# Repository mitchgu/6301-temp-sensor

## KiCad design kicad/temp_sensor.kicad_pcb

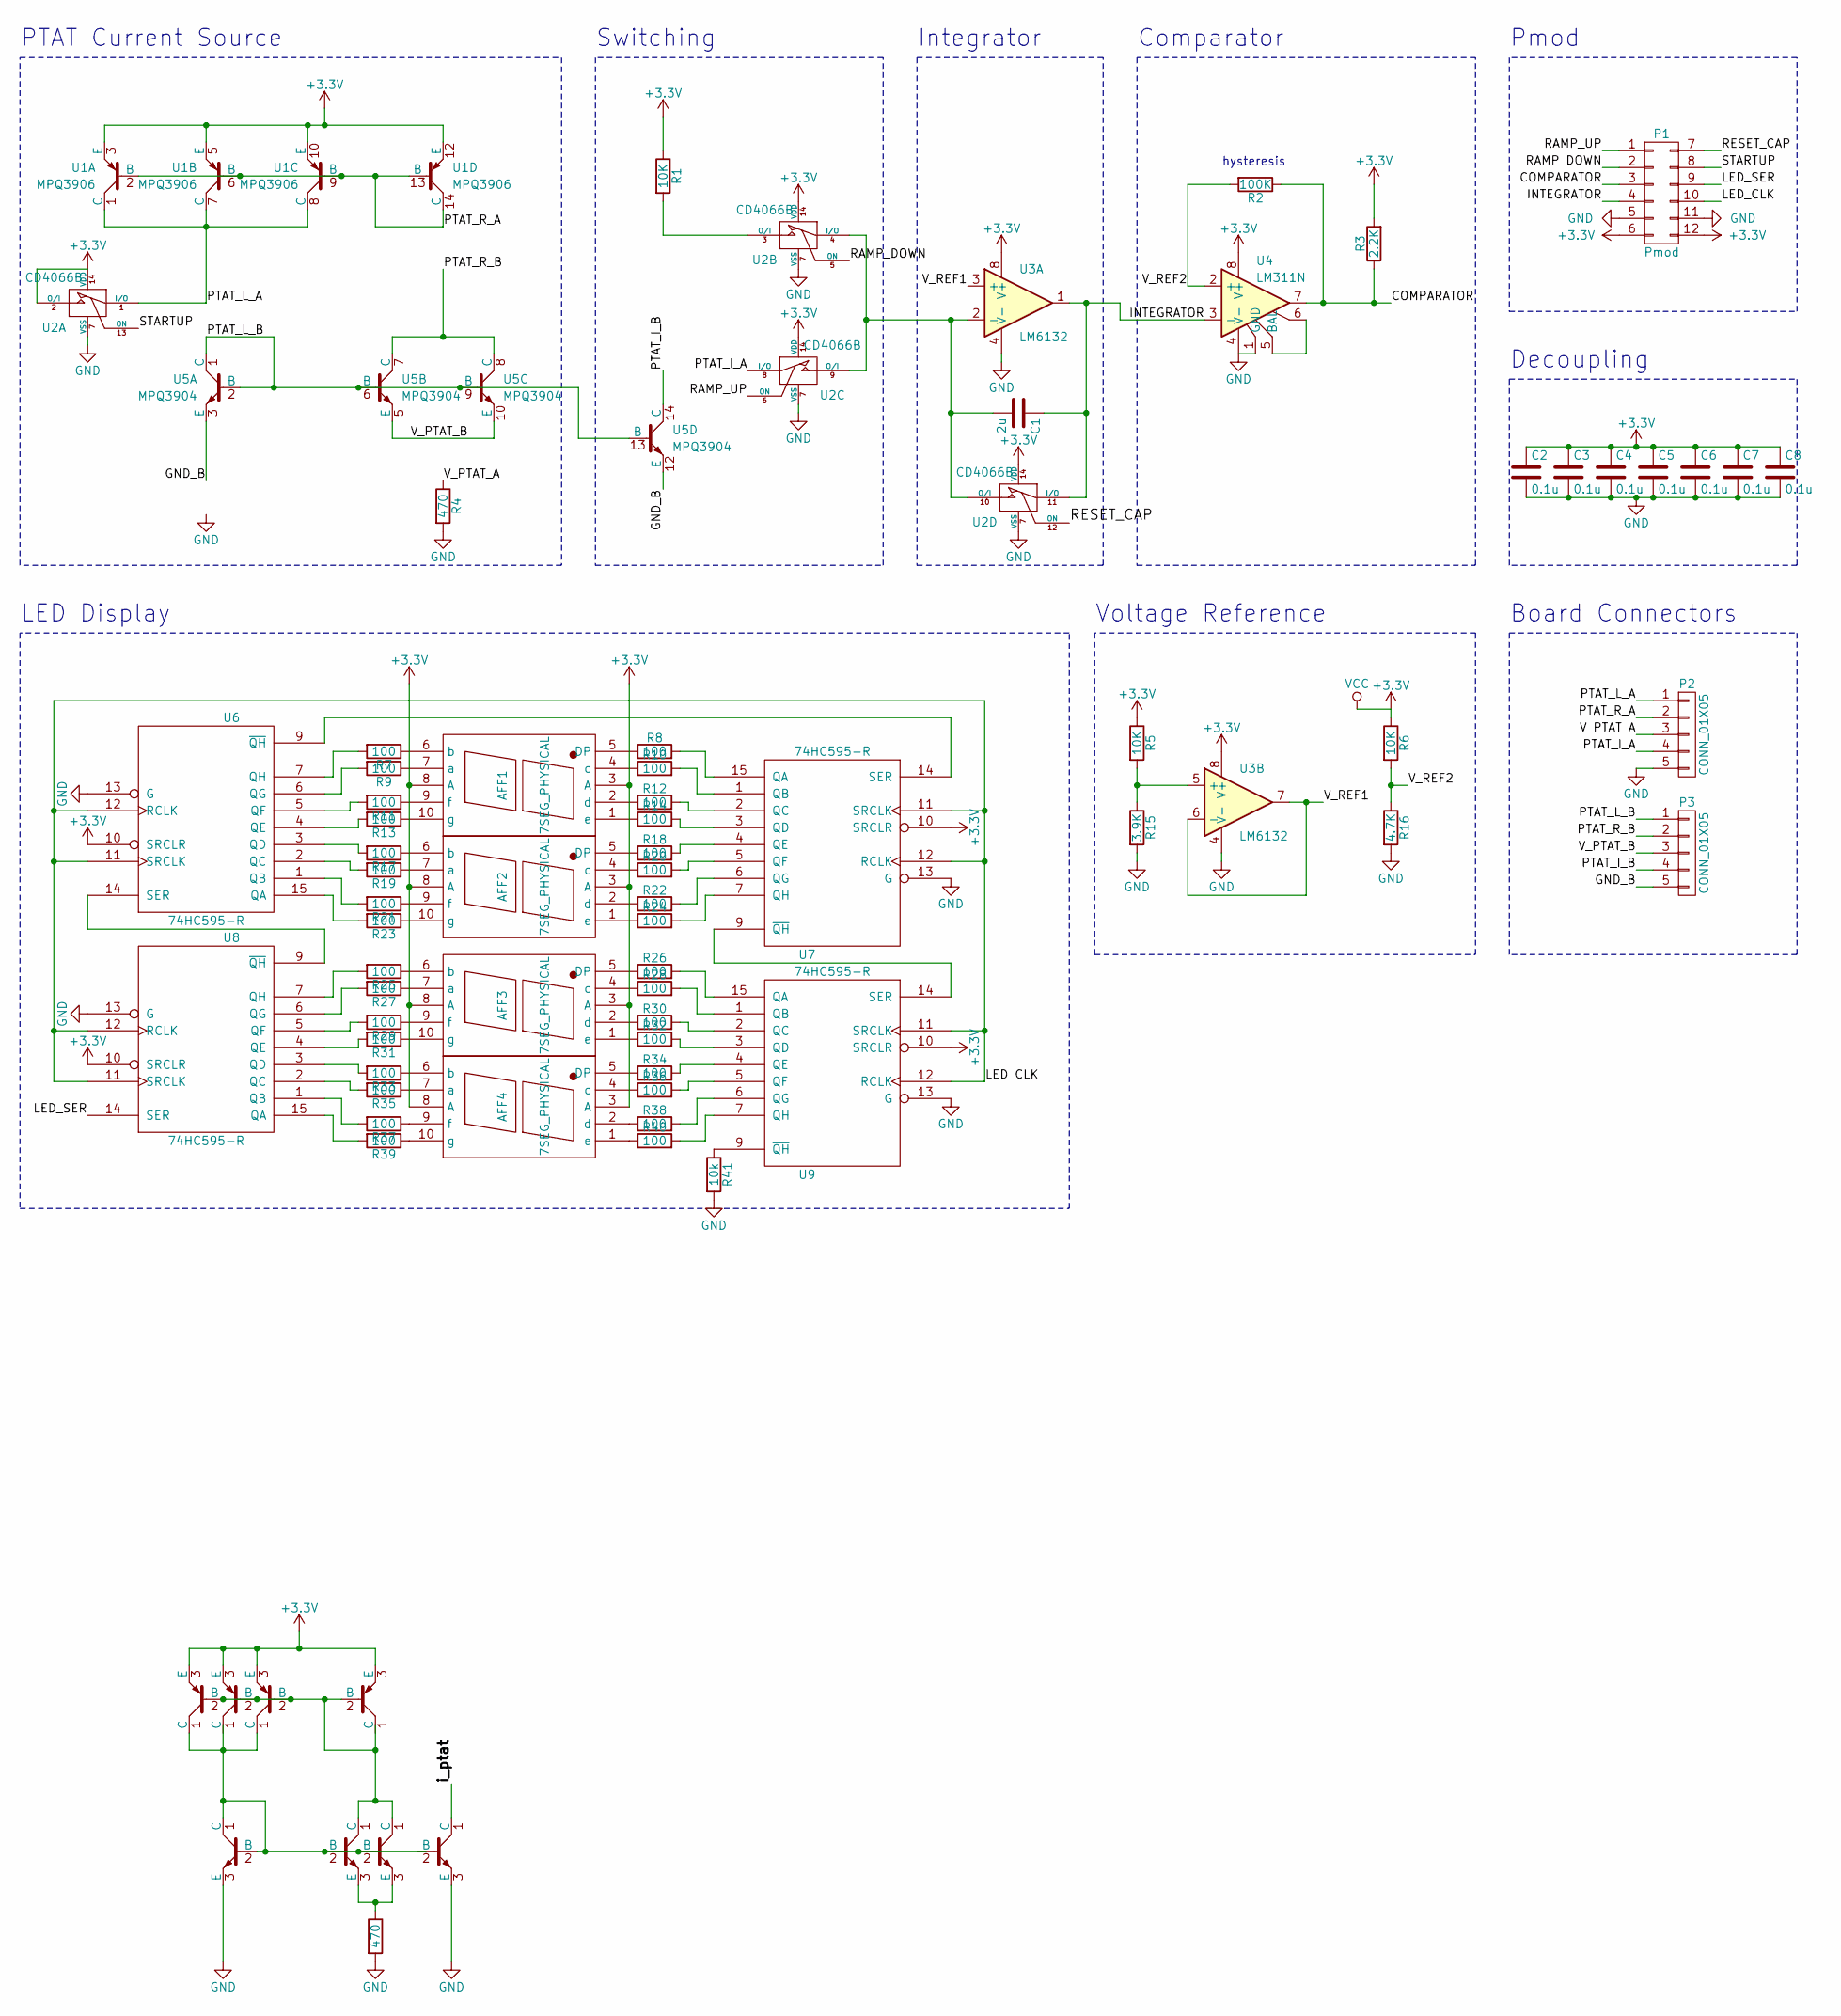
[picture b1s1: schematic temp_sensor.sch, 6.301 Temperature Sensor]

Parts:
AFF1, AFF2, AFF3, AFF4: 7SEG_PHYSICAL; 7SegmentLED_LTS6760_LTS6780
C1: 2u; C_Rect_L13_W6_H12_P10
C2, C3, C4, C5, C6, C7, C8: 0.1u; C_0805_HandSoldering
P1: Pmod; Pmod_Male
P2, P3: CONN_01X05; Pin_Header_Straight_1x05
R1, R5, R6: 10K; Resistor_Horizontal_RM7mm
R2: 100K; Resistor_Horizontal_RM7mm
R3: 2.2K; Resistor_Horizontal_RM7mm
R4: 470; Resistor_Horizontal_RM7mm
R7, R8, R9, R10, R11, R12, R13, R14, R17, R18, R19, R20, R21, R22, R23, R24, R25, R26, R27, R28, R29, R30, R31, R32, R33, R34, R35, R36, R37, R38, R39, R40: 100; R_0805_HandSoldering
R15: 3.9K; Resistor_Horizontal_RM7mm
R16: 4.7K; Resistor_Horizontal_RM7mm
R41: 10k; Resistor_Horizontal_RM7mm
U1: MPQ3906; DIP-14_W7.62mm
U2: CD4066B; DIP-14_W7.62mm
U3: LM6132; DIP-8_W7.62mm
U4: LM311N; DIP-8_W7.62mm
U5: MPQ3904; DIP-14_W7.62mm
U6, U7, U8, U9: 74HC595-R; DIP-16_W7.62mm

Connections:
+3V3: AFF1.3 (A), AFF1.8 (A), AFF2.3 (A), AFF2.8 (A), AFF3.3 (A), AFF3.8 (A), AFF4.3 (A), AFF4.8 (A), C2.1, C3.1, C4.1, C5.1, C6.1, C7.1, C8.1, P1.6, P1.12, R1.1, R3.2, R5.1, R6.1, U1.3 (E), U1.5 (E), U1.10 (E), U1.12 (E), U2.2 (O/I), U2.14 (VDD), U3.8 (V+), U4.8 (V+), U6.10 (SRCLR), U6.16 (VCC), U7.10 (SRCLR), U7.16 (VCC), U8.10 (SRCLR), U8.16 (VCC), U9.10 (SRCLR), U9.16 (VCC)
/COMPARATOR: P1.3, R2.1, R3.1, U4.7
/INTEGRATOR: C1.1, P1.4, U2.11 (I/O), U3.1, U4.3 (-)
/LED_CLK: P1.10, U6.11 (SRCLK), U6.12 (RCLK), U7.11 (SRCLK), U7.12 (RCLK), U8.11 (SRCLK), U8.12 (RCLK), U9.11 (SRCLK), U9.12 (RCLK)
/LED_SER: P1.9, U8.14 (SER)
/PTAT_I_A: P2.4, U2.8 (I/O)
/PTAT_L_A: P2.1, U1.1 (C), U1.7 (C), U1.8 (C), U2.1 (I/O)
/PTAT_R_A: P2.2, U1.2 (B), U1.6 (B), U1.9 (B), U1.13 (B), U1.14 (C)
/RAMP_DOWN: P1.2, U2.5 (ON)
/RAMP_UP: P1.1, U2.6 (ON)
/RESET_CAP: P1.7, U2.12 (ON)
/STARTUP: P1.8, U2.13 (ON)
/V_PTAT_A: P2.3, R4.1
/V_REF1: U3.3 (+), U3.6 (-), U3.7
/V_REF2: R2.2, R6.2, R16.1, U4.2 (+)
GND: C2.2, C3.2, C4.2, C5.2, C6.2, C7.2, C8.2, P1.5, P1.11, P2.5, R4.2, R15.2, R16.2, R41.2, U2.7 (VSS), U3.4 (V-), U4.1 (GND), U4.4 (V-), U6.8 (GND), U6.13 (G), U7.8 (GND), U7.13 (G), U8.8 (GND), U8.13 (G), U9.8 (GND), U9.13 (G)
unnamed: AFF1.1 (e), R14.1
unnamed: AFF1.2 (d), R12.1
unnamed: AFF1.4 (c), R10.1
unnamed: AFF1.5 (DP), R8.1
unnamed: AFF1.6 (b), R7.1
unnamed: AFF1.7 (a), R9.1
unnamed: AFF1.9 (f), R11.1
unnamed: AFF1.10 (g), R13.1
unnamed: AFF2.1 (e), R24.1
unnamed: AFF2.2 (d), R22.1
unnamed: AFF2.4 (c), R20.1
unnamed: AFF2.5 (DP), R18.1
unnamed: AFF2.6 (b), R17.1
unnamed: AFF2.7 (a), R19.1
unnamed: AFF2.9 (f), R21.1
unnamed: AFF2.10 (g), R23.1
unnamed: AFF3.1 (e), R32.1
unnamed: AFF3.2 (d), R30.1
unnamed: AFF3.4 (c), R28.1
unnamed: AFF3.5 (DP), R26.1
unnamed: AFF3.6 (b), R25.1
unnamed: AFF3.7 (a), R27.1
unnamed: AFF3.9 (f), R29.1
unnamed: AFF3.10 (g), R31.1
unnamed: AFF4.1 (e), R40.1
unnamed: AFF4.2 (d), R38.1
unnamed: AFF4.4 (c), R36.1
unnamed: AFF4.5 (DP), R34.1
unnamed: AFF4.6 (b), R33.1
unnamed: AFF4.7 (a), R35.1
unnamed: AFF4.9 (f), R37.1
unnamed: AFF4.10 (g), R39.1
unnamed: C1.2, U2.4 (I/O), U2.9 (O/I), U2.10 (O/I), U3.2 (-)
unnamed: P3.1, U5.1 (C), U5.2 (B), U5.6 (B), U5.9 (B), U5.13 (B)
unnamed: P3.2, U5.7 (C), U5.8 (C)
unnamed: P3.3, U5.5 (E), U5.10 (E)
unnamed: P3.4, U5.14 (C)
unnamed: P3.5, U5.3 (E), U5.12 (E)
unnamed: R1.2, U2.3 (O/I)
unnamed: R7.2, U6.7 (QH)
unnamed: R8.2, U7.15 (QA)
unnamed: R9.2, U6.6 (QG)
unnamed: R10.2, U7.1 (QB)
unnamed: R11.2, U6.5 (QF)
unnamed: R12.2, U7.2 (QC)
unnamed: R13.2, U6.4 (QE)
unnamed: R14.2, U7.3 (QD)
unnamed: R5.2, R15.1, U3.5 (+)
unnamed: R17.2, U6.3 (QD)
unnamed: R18.2, U7.4 (QE)
unnamed: R19.2, U6.2 (QC)
unnamed: R20.2, U7.5 (QF)
unnamed: R21.2, U6.1 (QB)
unnamed: R22.2, U7.6 (QG)
unnamed: R23.2, U6.15 (QA)
unnamed: R24.2, U7.7 (QH)
unnamed: R25.2, U8.7 (QH)
unnamed: R26.2, U9.15 (QA)
unnamed: R27.2, U8.6 (QG)
unnamed: R28.2, U9.1 (QB)
unnamed: R29.2, U8.5 (QF)
unnamed: R30.2, U9.2 (QC)
unnamed: R31.2, U8.4 (QE)
unnamed: R32.2, U9.3 (QD)
unnamed: R33.2, U8.3 (QD)
unnamed: R34.2, U9.4 (QE)
unnamed: R35.2, U8.2 (QC)
unnamed: R36.2, U9.5 (QF)
unnamed: R37.2, U8.1 (QB)
unnamed: R38.2, U9.6 (QG)
unnamed: R39.2, U8.15 (QA)
unnamed: R40.2, U9.7 (QH)
unnamed: R41.1, U9.9 (~QH)
unnamed: U4.5 (BAL), U4.6
unnamed: U6.9 (~QH), U7.14 (SER)
unnamed: U6.14 (SER), U8.9 (~QH)
unnamed: U7.9 (~QH), U9.14 (SER)

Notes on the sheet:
PTAT Current Source
Switching
Integrator
Comparator
hysteresis
Pmod
Voltage Reference
LED Display
Decoupling
Board Connectors

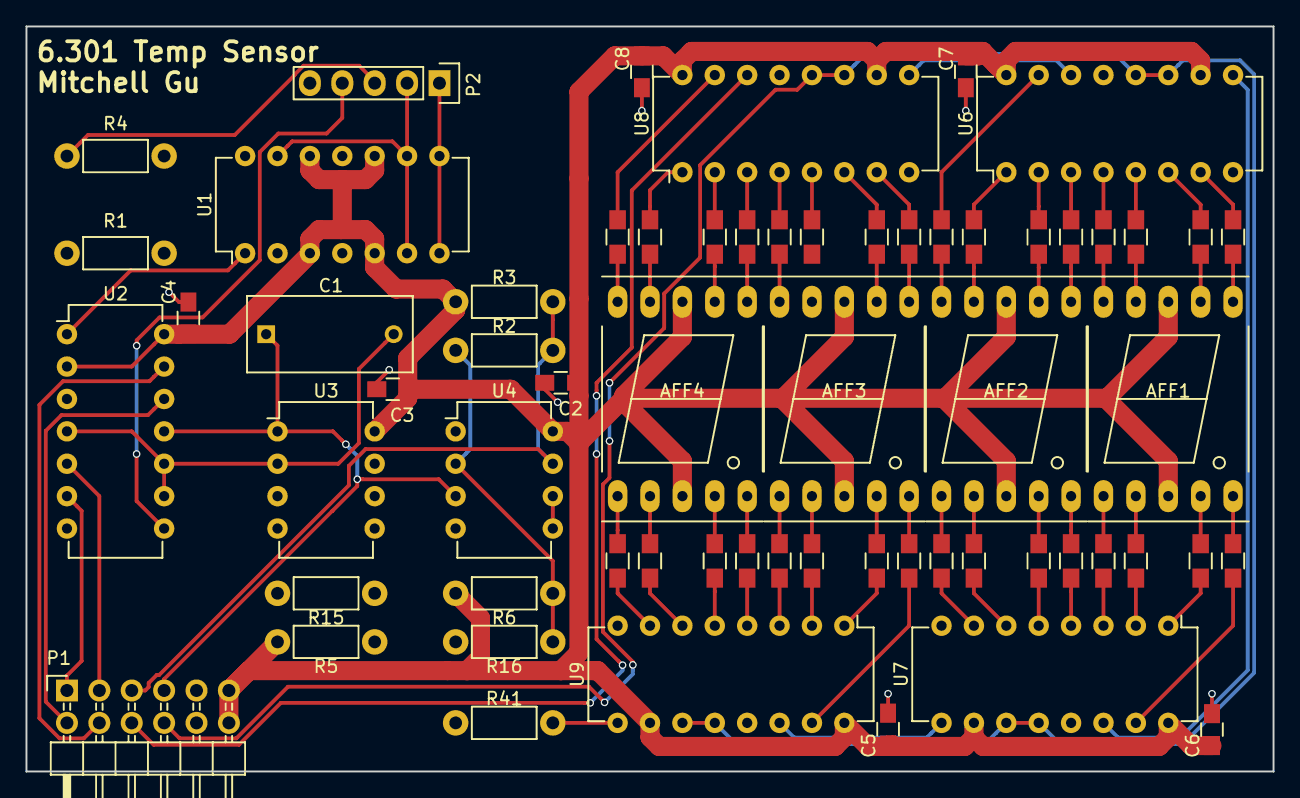
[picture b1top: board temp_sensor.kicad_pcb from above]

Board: 2 copper layers, 97.8 x 58.4 mm, 63 parts (0 on the bottom side), 88 nets.

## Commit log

2018-03-14 Smaller file size report
